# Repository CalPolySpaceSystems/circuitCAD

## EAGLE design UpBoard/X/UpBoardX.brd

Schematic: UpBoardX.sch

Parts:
C1: 10pF; C0603
C2, C3, C4, C5, C6, C7: 22pF; C0603
C8: 10n; C0603
C11: 1uF; C0603
C12, C13, C14, C15, C16: 10uF; A/3216-18R
CN1, CN2, CN3, CN4: 100nF; 1206-4
D3, D4, D5, D6, D7, D8, D9: DSOD323; SOD323
ERASE: 1000P; B3U-1000P
ERASE_EN: 0R; R0402
IC1: SAM3X8E(ARDUINO); 144-LEAD_LQFP
IC2: MEGA16U2-MU; QFN32
J1: 2POSTERMINALBLOCK.25"PITCH; OSTYK22102030
JP1: PINHD-2X5; 2X05
JP2: A109214; 735
L: LEDCHIPLED_0805; CHIPLED_0805
L1, L2, L3: L-EU0402; C0402
LS1: AI-1440-TWT-24V-2-R; AI-1440-TWT-24-2-R
LSP1: LSP10
PWR: LEDCHIPLED_0805; CHIPLED_0805
Q1, Q2, Q3, Q4: FDS5680; SO-8
Q5: SSMJ328R,LF; SOT23
Q6, Q8: 2N7002E; NMINI3-R1-B
R1, R2: 22; R0603
R3, R4: 39; R0603
R5, R6, R7, R8: 65; R0603
R9, R10, R11, R12, R13, R14: 1k; R0603
R15: 6.8K; R0603
R16, R17, R18, R20, R21, R22, R23: 10k; R0603
R19: 10K; R0402
R24: 1M; R0603
R25, R26, R27, R28, R29, R30, R31, R32, R33, R34, R35, R36: R-US_R0603; R0603
R37, R38: 0R; R0402
R39: 0R; R0603
RESET: 1000P; B3U-1000P
RN1: 10K; CTS742C083
RN2: 1k; CTS742C083
RST_EN: 0R; R0402
RV1, RV2, RV3, RV4, RV5: VARISTORCN0603; CT/CN0603
RX: LEDCHIPLED_0805; CHIPLED_0805
SJ1, SJ2, SJ3, SJ4, SJ5: SJ2W; SJ_2
TX: LEDCHIPLED_0805; CHIPLED_0805
U$2: CONN_MICROSD
US1, US2: USBMINIB; USB-MINIB
X1, X2: COMS; 15POSD-SUB
X3: GP; 15POSD-SUB
X4: CTRL/PYRO; 9POSD-SUB
XA1: DF12-20PIN_CONNECTOR_HEADER; DF12-HEADER
Y1: FH1200001; MINISMD
Y2: ABS05; FC-12M
Y3: 406C35D16M00000; 4SMD

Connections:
1.8V: C13.+, CN2.P$1 (1), CN2.P$2 (1), CN2.P$3 (1), CN2.P$4 (1), CN3.P$1 (1), CN3.P$2 (1), IC1.P$10 (VDDCORE), IC1.P$45 (VDDCORE), IC1.P$56 (VDDOUT), IC1.P$61 (VDDCORE), IC1.P$104 (VDDCORE), IC1.P$124 (VDDCORE), L1.1
3.3V: C8.1, C12.+, CN3.P$3 (1), CN3.P$4 (1), CN4.P$1 (1), CN4.P$2 (1), CN4.P$3 (1), CN4.P$4 (1), ERASE_EN.2, IC1.P$11 (VDDIO), IC1.P$52 (VDDBU), IC1.P$57 (VDDIN), IC1.P$62 (VDDIO), IC1.P$105 (VDDIO), IC1.P$125 (VDDIO), JP1.1, L2.1, L3.1, Q5.3 (S), R5.2, R6.2, R7.2, R8.2, R19.2, RN1.5, RN1.6, RN1.7, RN1.8, RN2.7, RN2.8, U$2.4 (4-VDD), X1.1, X2.1, X3.1, XA1.P$1; also elsewhere on the board
5V: D8.2 (A), D9.1 (C), R9.1, US1.VBUS; also elsewhere on the board
12V: D7.2 (A), R11.1, R12.1, R13.1, R14.1, X1.3, X2.3, X3.3, X4.1, XA1.P$2, XA1.P$3; also elsewhere on the board
A0: IC1.P$78 (PA16(A0)), X2.14
A1: IC1.P$79 (PA24(A1)), X2.15
A2: IC1.P$80 (PA23(A2)), X1.14
A3: IC1.P$81 (PA22(A3)), X1.15
A4: IC1.P$82 (PA6(A4)), X3.14
A5: IC1.P$83 (PA4(A5)), X3.15
A6: IC1.P$84 (PA3(A6)), R26.1, R32.2
A7: IC1.P$85 (PA2(A7)), R27.1, R33.2
A8: IC1.P$88 (PB17(A8)), R28.1, R34.2
A9: IC1.P$89 (PB18(A9)), R29.1, R35.2
A10: IC1.P$90 (PB19(A10)), R30.1, R36.2
AIN6: R26.2, X4.8
AIN7: R27.2, X4.9
AIN8: R28.2, XA1.P$17
AIN9: R29.2, XA1.P$18
AIN10: R30.2, XA1.P$19
AREF: R25.2, SJ1.3, SJ2.3, SJ3.3, SJ4.3, SJ5.3
AREF0/D51: SJ1.2, XA1.P$16
AREF1/D3: SJ2.2, X1.13
AREF2/D8: SJ3.2, X2.13
AREF3/D25: SJ4.2, X3.13
AREF4/D9: SJ5.2, X4.7
AVDREF: IC1.P$75 (AVDREF), R25.1, R31.2
BD+: R1.1, RV4.1, US2.D+
BD-: R2.1, RV5.1, US2.D-
CFG_D+: IC2.P29 (D+), R1.2
CFG_D-: IC2.P30 (D-), R2.2
CFG_MISO: IC2.P17 (PB3), JP2.P1
CFG_MOSI: IC2.P16 (PB2), JP2.P4
CFG_OSC2: C3.1, IC2.P2 (PC0/XTAL2), R24.2, Y3.P1 (1)
CFG_RESET: IC2.P24 (PC1/RESET), JP2.P5
CFG_SCK: IC2.P15 (PB1), JP2.P3
D3: IC1.P$139 (PC28(D3)), SJ2.1
D4: IC1.P$137 (PC26(D4))
D5: IC1.P$136 (PC25(D5))
D6: IC1.P$135 (PC24(D6)), X2.11
D7: IC1.P$134 (PC23(D7)), X2.12
D8: IC1.P$133 (PC22(D8)), SJ3.1
D9: IC1.P$132 (PC21(D9)), SJ5.1
D11: IC1.P$20 (PD7(D11)), U$2.2 (2-CD/DAT3)
D12: IC1.P$21 (PD8(D12)), Q6.1 (G), R17.1
D13: IC1.P$68 (PB27(D13/L)), Q8.1 (G), R16.2
D23: IC1.P$7 (PA14(D23)), X3.11
D24: IC1.P$8 (PA15(D24)), X3.12
D25: IC1.P$13 (PD0(D25)), SJ4.1
D37: IC1.P$63 (PC5(D37)), Q4.4 (G), R23.1
D38: IC1.P$64 (PC6(D38)), Q3.4 (G), R22.1
D39: IC1.P$65 (PC7(D39)), Q2.4 (G), R21.1
D40: IC1.P$66 (PC8(D40)), Q1.4 (G), R20.1
D44: IC1.P$101 (PC19(D44))
D46: IC1.P$99 (PC17(D46)), XA1.P$11
D47: IC1.P$98 (PC16(D47)), XA1.P$12
D48: IC1.P$97 (PC15(D48)), XA1.P$13
D49: IC1.P$96 (PC14(D49)), XA1.P$14
D50: IC1.P$95 (PC13(D50)), XA1.P$15
D51: IC1.P$94 (PC12(D51)), SJ1.1
D+: IC1.P$37 (DHSDP), R3.1, RV1.1, US1.D+
D-: IC1.P$38 (DHSDM), R4.1, RV2.1, US1.D-
ERASE_CMD: IC2.P23 (PC6), Q5.1 (G), R19.1
F0/X+: D6.1 (C), Q4.5 (D), Q4.6 (D), Q4.7 (D), Q4.8 (D), R11.2, X4.2
F1/X-: D5.1 (C), Q3.5 (D), Q3.6 (D), Q3.7 (D), Q3.8 (D), R12.2, X4.3
F2/Y+: D4.1 (C), Q2.5 (D), Q2.6 (D), Q2.7 (D), Q2.8 (D), R13.2, X4.4
F3/Y-: D3.1 (C), Q1.5 (D), Q1.6 (D), Q1.7 (D), Q1.8 (D), R14.2, X4.5
GND: C1.2, C2.2, C3.2, C4.1, C5.1, C6.2, C7.2, C11.2, C12.-, C13.-, C14.-, C15.-, C16.-, CN1.P$2 (1), CN1.P$3 (1), CN1.P$4 (1), CN2.P$5 (2), CN2.P$6 (2), CN2.P$7 (2), CN2.P$8 (2), CN3.P$5 (2), CN3.P$6 (2), CN3.P$7 (2), CN3.P$8 (2), CN4.P$5 (2), CN4.P$6 (2), CN4.P$7 (2), CN4.P$8 (2), D3.2 (A), D4.2 (A), D5.2 (A), D6.2 (A), IC1.P$12 (GND), IC1.P$33 (GNDPLL), IC1.P$44 (GNDUTMI), IC1.P$54 (GNDBU), IC1.P$58 (GND), IC1.P$74 (GNDANA), IC1.P$106 (GND), IC1.P$126 (GND), IC2.P3 (GND), IC2.P28 (UGND), IC2.TH, J1.P$2, JP1.3, JP1.5, JP1.9, JP2.P6, LSP1.MP, PWR.C, Q1.1 (S), Q1.2 (S), Q1.3 (S), Q2.1 (S), Q2.2 (S), Q2.3 (S), Q3.1 (S), Q3.2 (S), Q3.3 (S), Q4.1 (S), Q4.2 (S), Q4.3 (S), Q6.2 (S), Q8.2 (S), R15.1, R16.1, R17.2, R18.2, R20.2, R21.2, R22.2, R23.2, R31.1, R32.1, R33.1, R34.1, R35.1, R36.1, R37.2, R38.2, RST_EN.2, RV1.2, RV2.2, RV3.2, RV4.2, RV5.2, U$2.6 (6-VSS), U$2.GND1, U$2.GND2, U$2.GND3, US1.GND, US2.GND, X1.2, X2.2, X3.2, X4.6, XA1.P$4, XA1.P$5, XA1.P$20, Y1.GND2 (2), Y1.GND4 (2), Y3.P2 (2), Y3.P4 (2); also elsewhere on the board
HV: D7.1 (C), D8.1 (C), R39.2
JTAG_SEL: IC1.P$46 (JTAGSEL), R38.1
JTAG_TCK: IC1.P$28 (PB28/TCK/SWCLK), JP1.4, RN1.2
JTAG_TDI: IC1.P$29 (PB29/TDI), JP1.8, RN1.3
JTAG_TDO: IC1.P$30 (PB30/TDO/TRACESWO), JP1.6
JTAG_TMS: IC1.P$31 (PB31/TMS/SWDIO), JP1.2, RN1.1
MISO: IC1.P$108 (PA25/SPI0_MISO(MISO)), U$2.7 (7-DAT0), X1.6, X2.6, X3.6, XA1.P$6
MOSI: IC1.P$109 (PA26/SPI0_MOSI(MOSI)), U$2.3 (3-CMO), X1.7, X2.7, X3.7, XA1.P$7
M_RESET: C8.2, IC1.P$47 (NRSTB), JP1.10, R10.1, RESET.P$2, RN1.4
unnamed: C11.1, IC2.P27 (UCAP)
unnamed: IC1.P$42 (DFSDP), R3.2
unnamed: C2.1, IC2.P1 (XTAL1), R24.1, Y3.P3 (3)
unnamed: RESET.P$1, RST_EN.1
unnamed: IC1.P$43 (DFSDM), R4.2
unnamed: IC2.P26 (PC4), R9.2
unnamed: IC2.P22 (PC7), R10.2
unnamed: ERASE.P$2, IC1.P$130 (PC0/ERASE), Q5.2 (D)
unnamed: ERASE.P$1, ERASE_EN.1
unnamed: IC2.P13 (PD7), R18.1
unnamed: C5.2, IC1.P$35 (XOUT), Y1.P3 (3)
unnamed: LS1.-, Q6.3 (D)
unnamed: C4.2, IC1.P$36 (XIN), Y1.P1 (1)
unnamed: C7.1, IC1.P$49 (XOUT32), Y2.2
unnamed: C6.1, IC1.P$48 (XIN32), Y2.1
unnamed: L.C, Q8.3 (D)
unnamed: LS1.+, R39.1
unnamed: L.A, R8.1
unnamed: C1.1, IC1.P$40 (VBG), R15.2
unnamed: PWR.A, R7.1
unnamed: R5.1, RX.A
unnamed: R6.1, TX.A
RX1: IC1.P$3 (PA10(RX1)), X1.4
RX2: IC1.P$5 (PA12(RX2)), X2.4
RX3/D15: IC1.P$18 (PD5(RX3)), X1.11
RX/D0: IC1.P$27 (PA8/URXD(RX0)), IC2.P9 (PD3), X3.4
RX_L: IC1.P$103 (PC30(RXLED)), RX.C
SCK: IC1.P$110 (PA27/SPI0_SPCK(SCK)), U$2.5 (5-CLK), X1.8, X2.8, X3.8, XA1.P$8
SCL: IC1.P$87 (PB13(SCL)), RN2.1, X1.10, X2.10, X3.10, XA1.P$10
SCL1: IC1.P$70 (PA18(SCL2))
SDA: IC1.P$86 (PB12(SDA)), RN2.2, X1.9, X2.9, X3.9, XA1.P$9
SDA1: IC1.P$9 (PA17(SDA1))
TST: IC1.P$51 (TST), R37.1
TX1: IC1.P$4 (PA11(TX1)), X1.5
TX2: IC1.P$6 (PA13(TX2)), X2.5
TX3/D14: IC1.P$17 (PD4(TX3)), X1.12
TX/D1: IC1.P$2 (PA9/UTXD(TX0)), IC2.P8 (PD2), X3.5
TX_L: IC1.P$107 (PA21(TXLED)), TX.C
UOTGID: IC1.P$129 (PB11(USB-ID)), RV3.1, US1.ID
UOTGVBOF: IC1.P$128 (PB10(USB-VBOF))
VBUS_CFG: D9.2 (A), IC2.P4 (VCC), IC2.P31 (UVCC), IC2.P32 (AVCC), JP2.P2, US2.VBUS
VDDANA: C15.+, CN1.P$7 (2), IC1.P$73 (VDDANA), L2.2
VDDPLL: C16.+, CN1.P$6 (2), IC1.P$34 (VDDPLL), L1.2
VDDUTMI: C14.+, CN1.P$8 (2), IC1.P$41 (VDDUTMI), L3.2
VIN: J1.P$1; also elsewhere on the board

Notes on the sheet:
Assy:
Size:
Revision:
Sheet 1 of 2
Date:
Sheet Title:
Project Title:
File: UpBoardX.sch
UBX Full Schematic
UpBoard X
C:/Users/Patrick Chizek/Pictures/CPSSLOGO.bmp
Cal Poly Space Systems

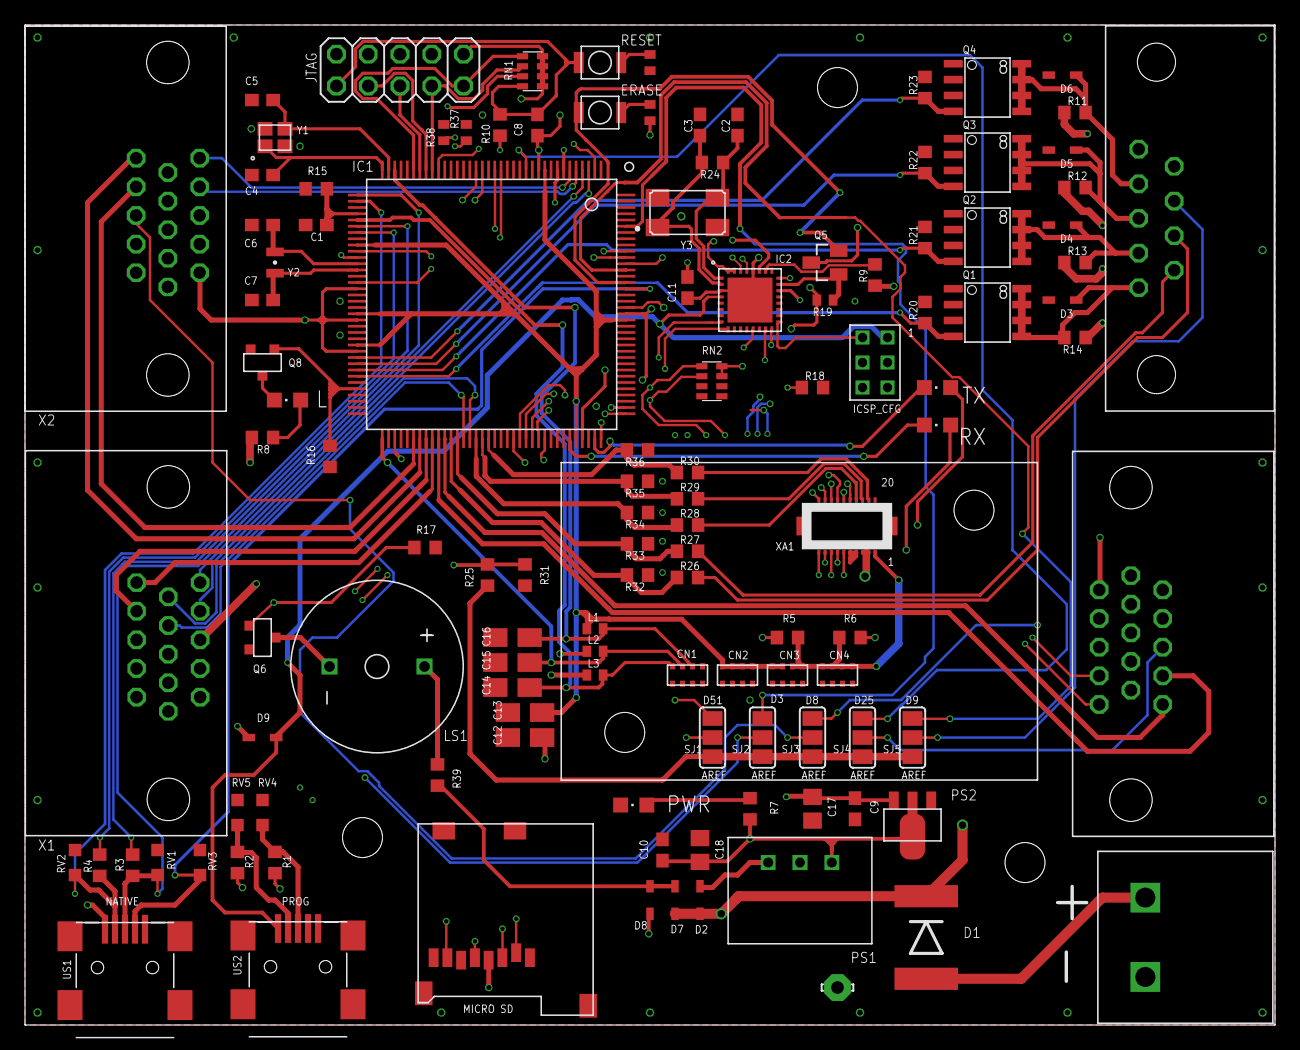
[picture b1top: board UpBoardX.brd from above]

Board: 4 copper layers, 100.0 x 80.0 mm, 120 parts (0 on the bottom side), 117 nets.

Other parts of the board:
PS1-1:C9, PS1-1:C10: 100nF; C0603
PS1-1:C17, PS1-1:C18: 100uF; C0805
PS1-1:D1: S10M-TP; DO-214AB
PS1-1:D2: SOD323
PS1-1:PS1: R-78B3.3-1.5
PS1-1:PS2: AZ1117C; SOT89

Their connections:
3.3V: PS1-1:C10.1, PS1-1:C18.1, PS1-1:PS1.3, PS1-1:PS2.2, PS1-1:PS2.2@1; also elsewhere on the board
5V: PS1-1:C9.1, PS1-1:C17.1, PS1-1:PS2.3; also elsewhere on the board
12V: PS1-1:D1.-, PS1-1:D2.2; also elsewhere on the board
GND: PS1-1:C9.2, PS1-1:C10.2, PS1-1:C17.2, PS1-1:C18.2, PS1-1:PS1.2, PS1-1:PS2.1; also elsewhere on the board
PS1-1:N$7: PS1-1:D2.1, PS1-1:PS1.1
VIN: PS1-1:D1.+; also elsewhere on the board
